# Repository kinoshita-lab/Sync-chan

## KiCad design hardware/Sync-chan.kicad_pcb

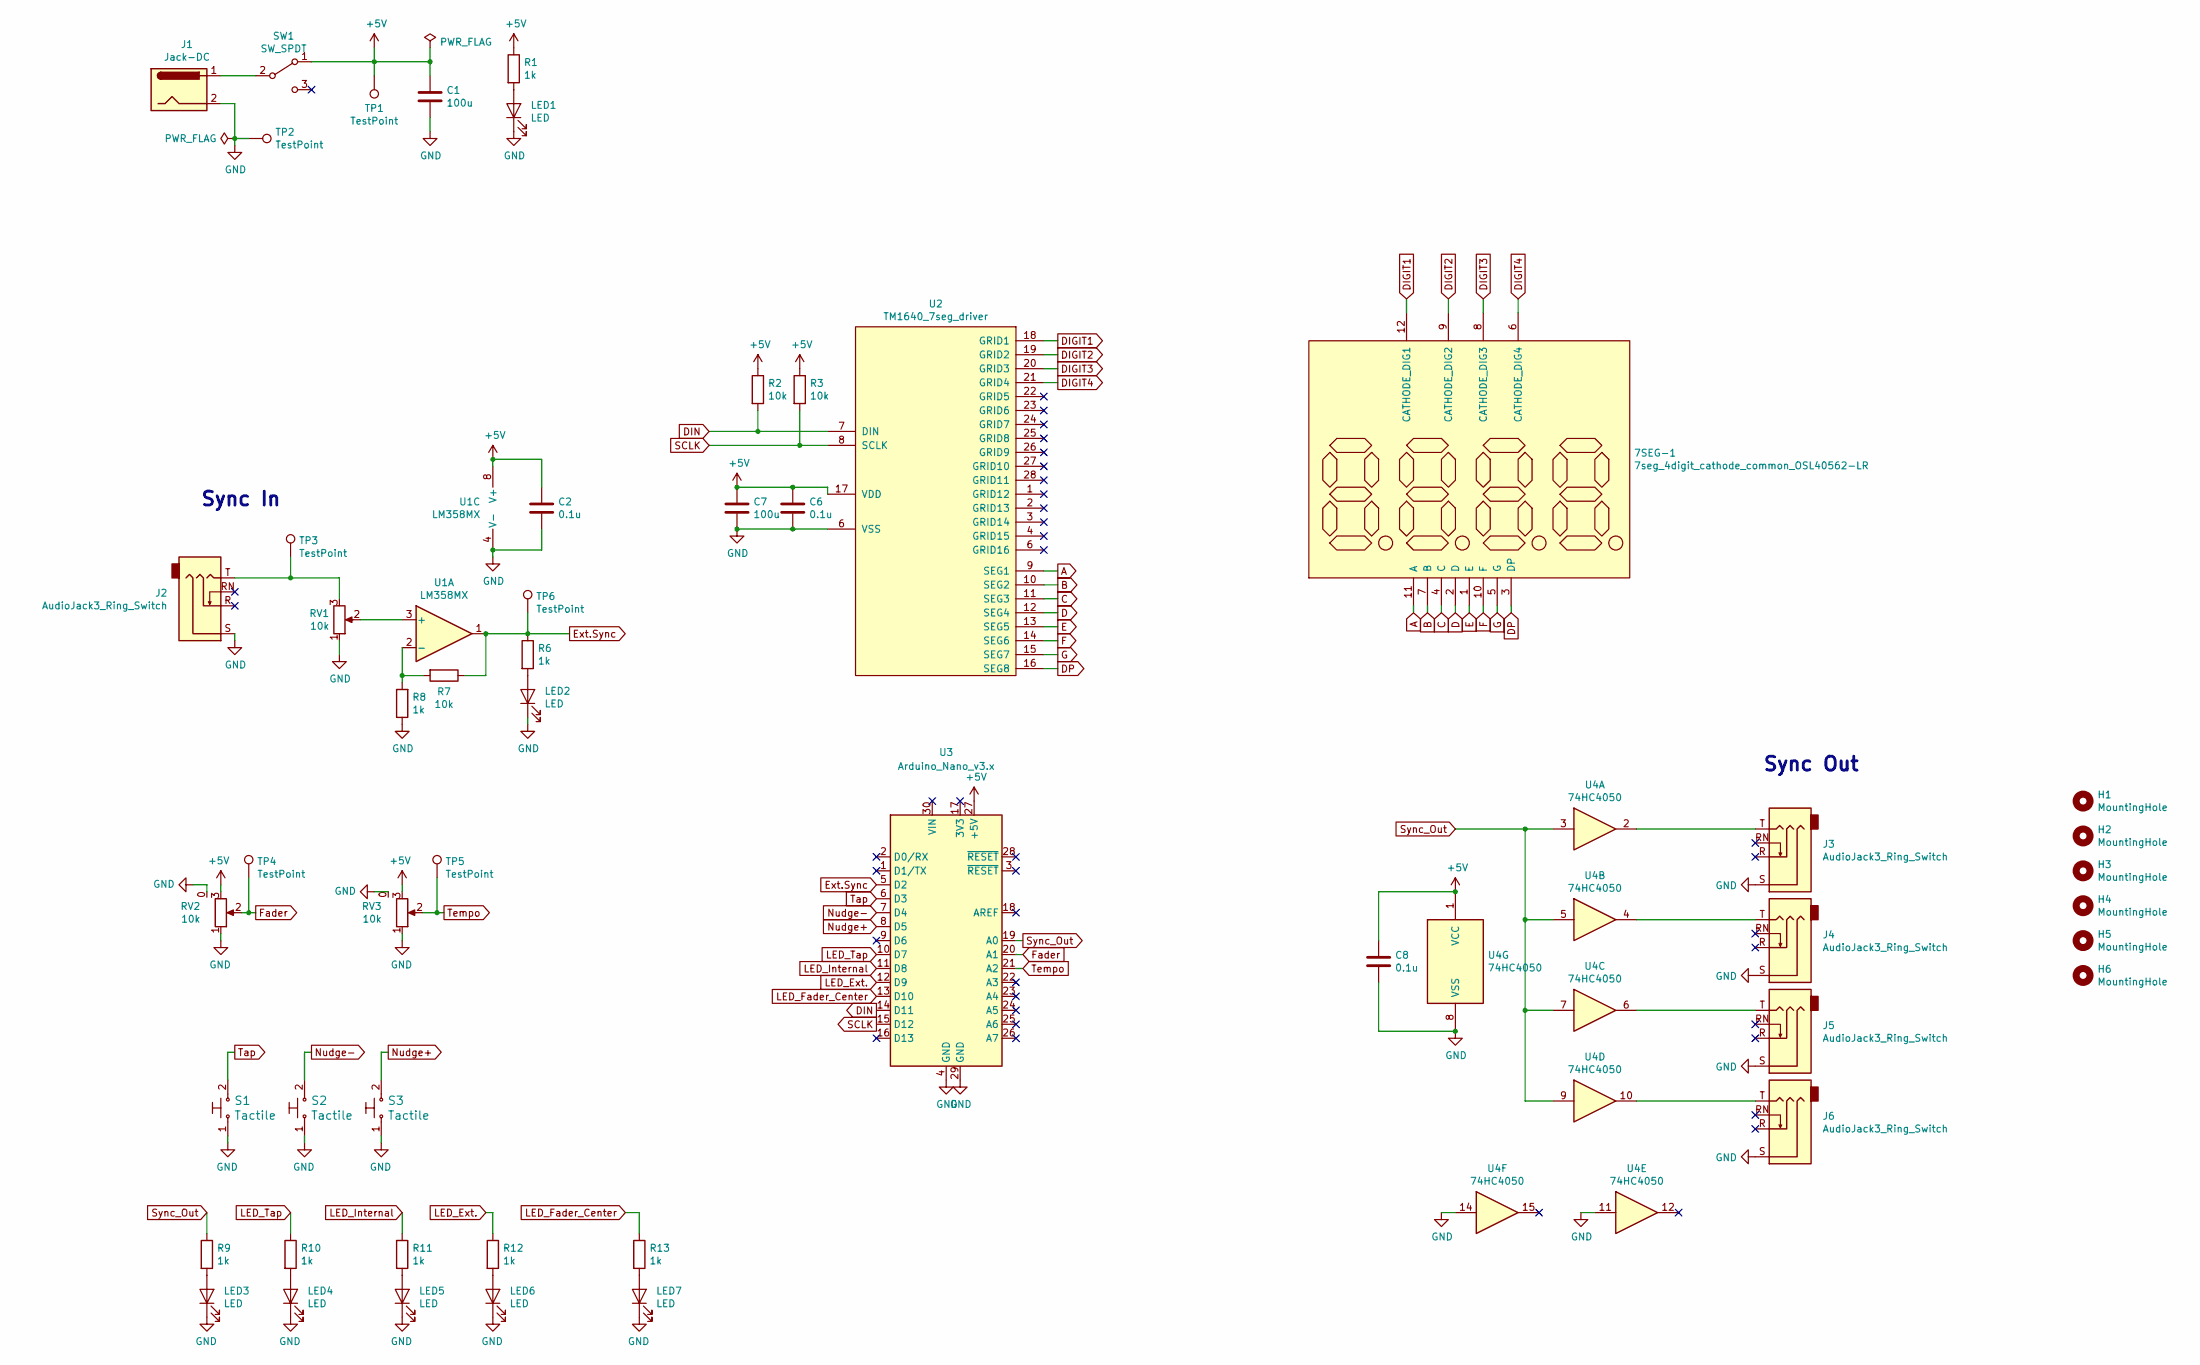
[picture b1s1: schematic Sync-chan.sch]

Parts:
7SEG-1: 7seg_4digit_cathode_common_OSL40562-LR
C1, C7: 100u; C_1206_HandSoldering
C2, C6, C8: 0.1u; C_0603_HandSoldering
H1, H2, H3, H4, H5, H6: MountingHole; MountingHole_3.2mm_M3
J1: Jack-DC; MRUSB-2B-D14NI-S306
J2, J3, J4, J5, J6: AudioJack3_Ring_Switch; 3.5mm_Stereo_Molex_0472570001
LED1, LED2, LED3, LED4, LED5, LED6, LED7: LED; LED_0603_HandSoldering_easier
R1, R6, R8, R9, R10, R11, R12, R13: 1k; R_0603_HandSoldering
R2, R3, R7: 10k; R_0603_HandSoldering
RV1: 10k; POT_TOCOS_GF063P1
RV2: 10k; POT_Slide_SL4515N
RV3: 10k; Potentiometer_Alps_RK09K_Horizontal_CORRECTED
S1, S2, S3: Tactile; SW_Tactile_Akizuki; MPN B3U-1000P; Digi-Key_PN SW1020CT-ND
SW1: SW_SPDT; SW_SPDT_2.5mm
TP1, TP2: TestPoint; TP_PAD_LARGE
TP3, TP4, TP5, TP6: TestPoint; TP_1PAD
U1: LM358MX; SOIC-8_3.9x4.9mm_Pitch1.27mm
U2: TM1640_7seg_driver; SOIC-28W_7.5x18.7mm_Pitch1.27mm
U3: Arduino_Nano_v3.x; Arduino_Nano
U4: 74HC4050; SOIC-16_3.9x9.9mm_Pitch1.27mm

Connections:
+5V: C1.1, C2.1, C6.1, C7.1, C8.1, R1.1, R2.1, R3.1, RV2.3, RV3.3, SW1.1 (A), TP1.1, U1.8 (V+), U2.17 (VDD), U3.27 (+5V), U4.1 (VCC)
A: 7SEG-1.11 (A), U2.9 (SEG1)
B: 7SEG-1.7 (B), U2.10 (SEG2)
C: 7SEG-1.4 (C), U2.11 (SEG3)
D: 7SEG-1.2 (D), U2.12 (SEG4)
DIGIT1: 7SEG-1.12 (CATHODE_DIG1), U2.18 (GRID1)
DIGIT2: 7SEG-1.9 (CATHODE_DIG2), U2.19 (GRID2)
DIGIT3: 7SEG-1.8 (CATHODE_DIG3), U2.20 (GRID3)
DIGIT4: 7SEG-1.6 (CATHODE_DIG4), U2.21 (GRID4)
DIN: R2.2, U2.7 (DIN), U3.14 (D11)
DP: 7SEG-1.3 (DP), U2.16 (SEG8)
E: 7SEG-1.1 (E), U2.13 (SEG5)
Ext.Sync: R6.1, R7.1, TP6.1, U1.1, U3.5 (D2)
F: 7SEG-1.10 (F), U2.14 (SEG6)
Fader: RV2.2, TP4.1, U3.20 (A1)
G: 7SEG-1.5 (G), U2.15 (SEG7)
GND: C1.2, C2.2, C6.2, C7.2, C8.2, J1.2, J2.S, J3.S, J4.S, J5.S, J6.S, LED1.1 (K), LED2.1 (K), LED3.1 (K), LED4.1 (K), LED5.1 (K), LED6.1 (K), LED7.1 (K), R8.1, RV1.1, RV2.0 (CASE), RV2.1, RV3.0 (CASE), RV3.1, S1.1, S2.1, S3.1, TP2.1, U1.4 (V-), U2.6 (GRID16), U3.4 (GND), U3.29 (GND), U4.8 (VSS), U4.11, U4.14
LED_Ext.: R12.1, U3.12 (D9)
LED_Fader_Center: R13.1, U3.13 (D10)
LED_Internal: R11.1, U3.11 (D8)
LED_Tap: R10.1, U3.10 (D7)
unnamed: J1.1, SW1.2 (B)
unnamed: J2.T, RV1.3, TP3.1
unnamed: J3.T, U4.2
unnamed: J4.T, U4.4
unnamed: J5.T, U4.6
unnamed: J6.T, U4.10
unnamed: LED1.2 (A), R1.2
unnamed: LED2.2 (A), R6.2
unnamed: LED3.2 (A), R9.2
unnamed: LED4.2 (A), R10.2
unnamed: LED5.2 (A), R11.2
unnamed: LED6.2 (A), R12.2
unnamed: LED7.2 (A), R13.2
unnamed: R7.2, R8.2, U1.2 (-)
unnamed: RV1.2, U1.3 (+)
Nudge+: S3.2, U3.8 (D5)
Nudge-: S2.2, U3.7 (D4)
SCLK: R3.2, U2.8 (SCLK), U3.15 (D12)
Sync_Out: R9.1, U3.19 (A0), U4.3, U4.5, U4.7, U4.9
Tap: S1.2, U3.6 (D3)
Tempo: RV3.2, TP5.1, U3.21 (A2)

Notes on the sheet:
Sync In
Sync Out

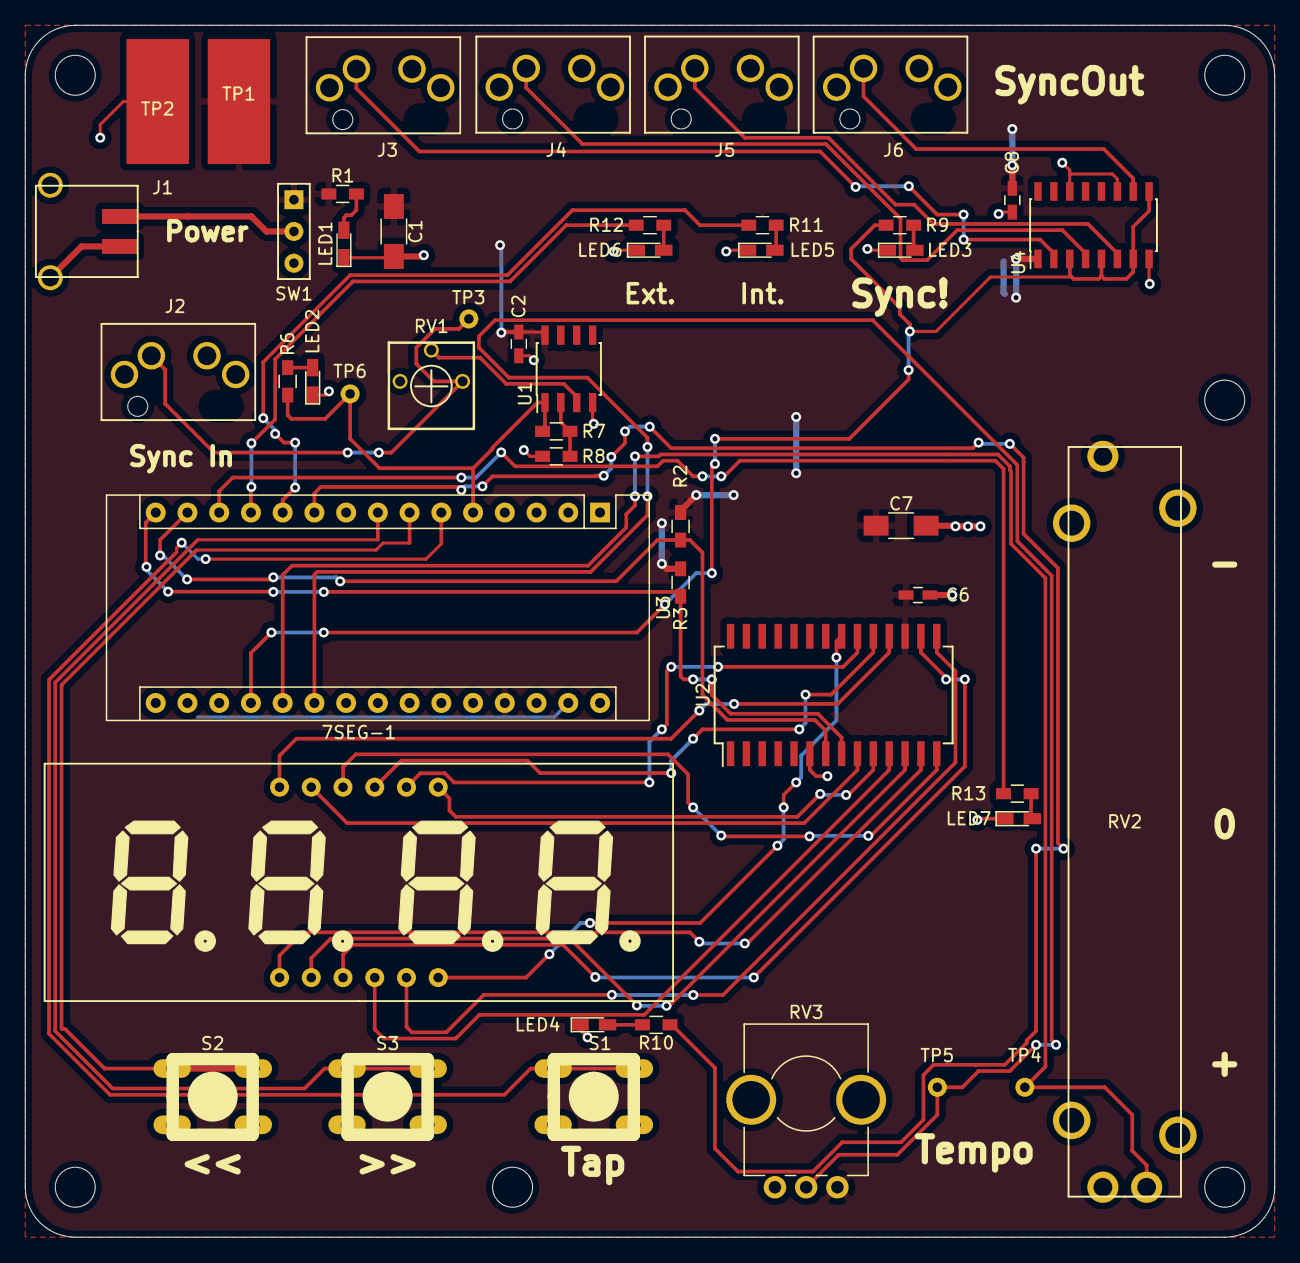
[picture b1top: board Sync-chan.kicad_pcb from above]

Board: 4 copper layers, 100.0 x 97.0 mm, 53 parts (0 on the bottom side), 42 nets.

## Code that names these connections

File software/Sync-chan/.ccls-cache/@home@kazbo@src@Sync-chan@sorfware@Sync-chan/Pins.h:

#pragma once
#include <Arduino.h>

#include <stdint.h>

namespace pin
{
struct DigitalPinConfig 
{
  uint8_t pinNo;
  uint8_t mode;
};

// digital pins
enum 
{
    Sync_Out = A0, 
    Ext_Sync = 2,
    Tap = 3, 
    NudgeMinus = 4,
    NudgePlus = 5,    
    Led_Tap = 7,
    Led_Internal = 8,
    Led_External = 9,
    Led_Fader_Center = 10,
    DIO_7Seg = 11,
    CLK_7Seg = 12,
    STB_7Seg = 13,
};

// analog pins
enum 
{
  Fader = 1,
  Tempo = 2,
};
}

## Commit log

2019-12-03 add prototype schem/pcb
2019-12-04 correct footprints
2019-12-10 modify pcb
2019-12-20 move folder, add TM1640 test code
2020-01-10 add hardware inspection program
2020-01-13 remove adc drift
2020-03-06 correct footprint molex trs connector
2020-03-06 replace C1, C7, modify TRS symbol
2020-03-06 implement microsec-precision timer with timerOne. seems working.
2020-03-06 move files
2020-03-23 implement basic features, format with clang-format
2020-03-23 add internal/external auto detection
2020-03-23 add tap tempo reset feature
2020-03-23 implement bpm detector
2020-03-24 debug external bpm detection
2020-03-24 seems everything working..!
2020-03-24 kinda refactoring
2020-03-24 beautify
2020-03-24 forget lighting tap led..
2020-05-16 Create LICENSE
